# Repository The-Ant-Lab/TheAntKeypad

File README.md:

# TheAntKeypad
The Ant Keypad project: hardware, firmware and software.

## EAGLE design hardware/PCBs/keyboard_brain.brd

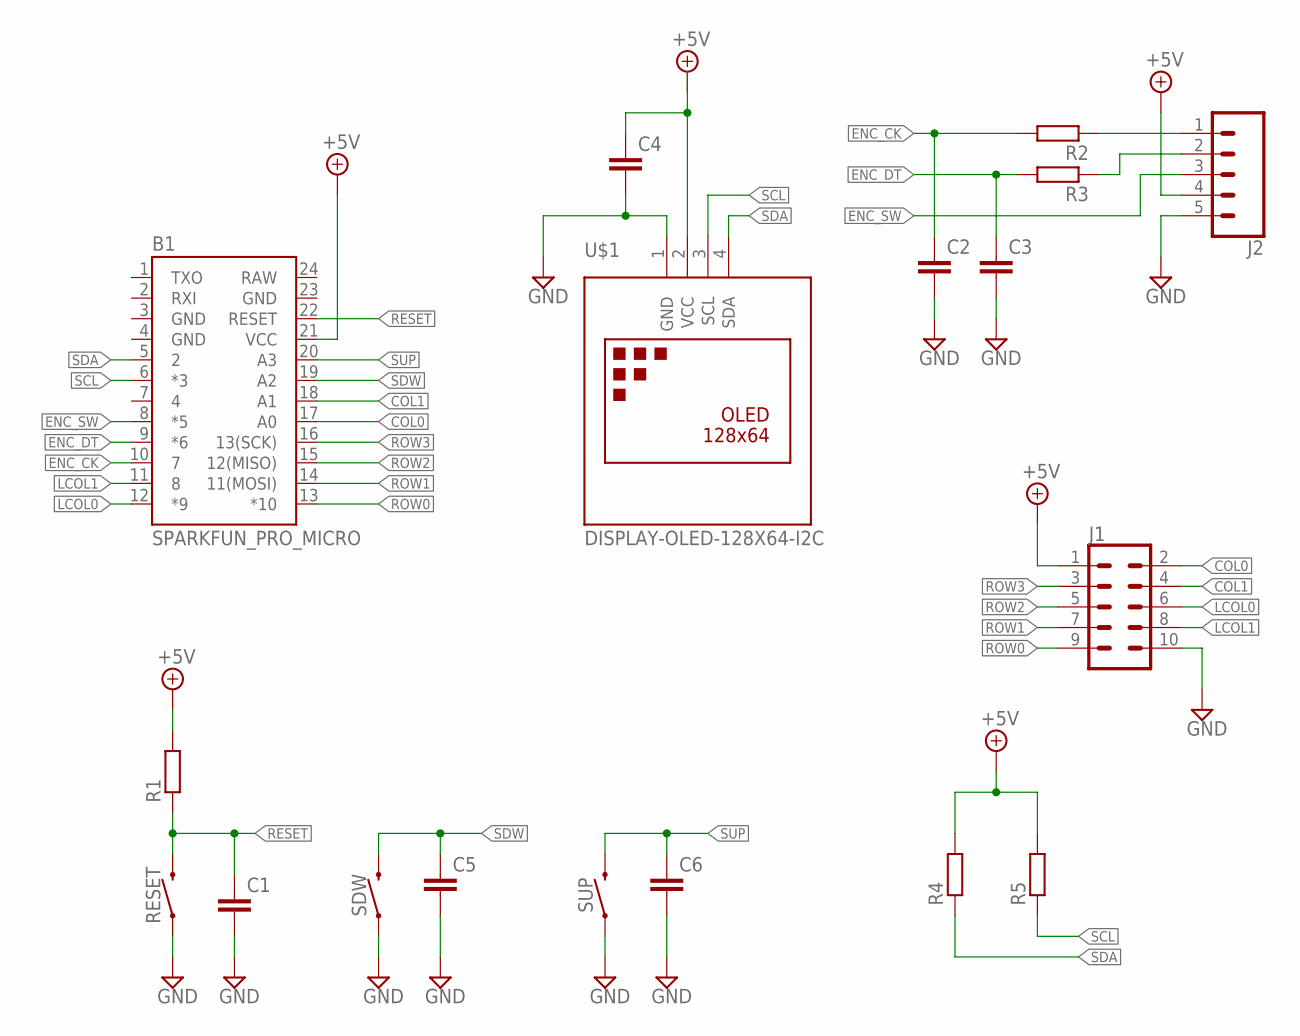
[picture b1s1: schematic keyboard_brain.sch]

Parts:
B1: SPARKFUN_PRO_MICRO
C1, C2, C3, C4, C5, C6: C-EUC0603K; C0603K
J1: CONN_05X2PTH; 2X5
J2: CONN_05; 1X05
R1, R2, R3, R4, R5: R-EU_R0603; R0603
RESET: MOMENTARY-SWITCH-SPST-PTH-6.0MM; TACTILE_SWITCH_PTH_6.0MM
SDW: MOMENTARY-SWITCH-SPST-SMD-5.2-REDUNDANT; TACTILE_SWITCH_SMD_5.2MM
SUP: MOMENTARY-SWITCH-SPST-SMD-5.2-REDUNDANT; TACTILE_SWITCH_SMD_5.2MM
U$1: DISPLAY-OLED-128X64-I2C

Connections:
+5V: B1.21 (VCC), C4.1, J1.1, J2.4, R1.2, R4.2, R5.2, U$1.2 (VCC)
COL0: B1.17 (A0), J1.2
COL1: B1.18 (A1), J1.4
ENC_CK: B1.10 (7), C2.1, R2.2
ENC_DT: B1.9 (*6), C3.1, R3.2
ENC_SW: B1.8 (*5), J2.3
GND: B1.3 (GND), B1.4 (GND), B1.23 (GND), C1.2, C2.2, C3.2, C4.2, C5.2, C6.2, J1.10, J2.5, RESET.1, SDW.1, SDW.2 (1), SUP.1, SUP.2 (1), U$1.1 (GND)
LCOL0: B1.12 (*9), J1.6
LCOL1: B1.11 (8), J1.8
unnamed: J2.1, R2.1
unnamed: J2.2, R3.1
RAW: B1.24 (RAW)
RESET: B1.22 (RESET), C1.1, R1.1, RESET.3 (2)
ROW0: B1.13 (*10), J1.9
ROW1: B1.14 (11(MOSI)), J1.7
ROW2: B1.15 (12(MISO)), J1.5
ROW3: B1.16 (13(SCK)), J1.3
SCL: B1.6 (*3), R5.1, U$1.3 (SCL)
SDA: B1.5 (2), R4.1, U$1.4 (SDA)
SDW: B1.19 (A2), C5.1, SDW.3 (2), SDW.4 (2)
SUP: B1.20 (A3), C6.1, SUP.3 (2), SUP.4 (2)

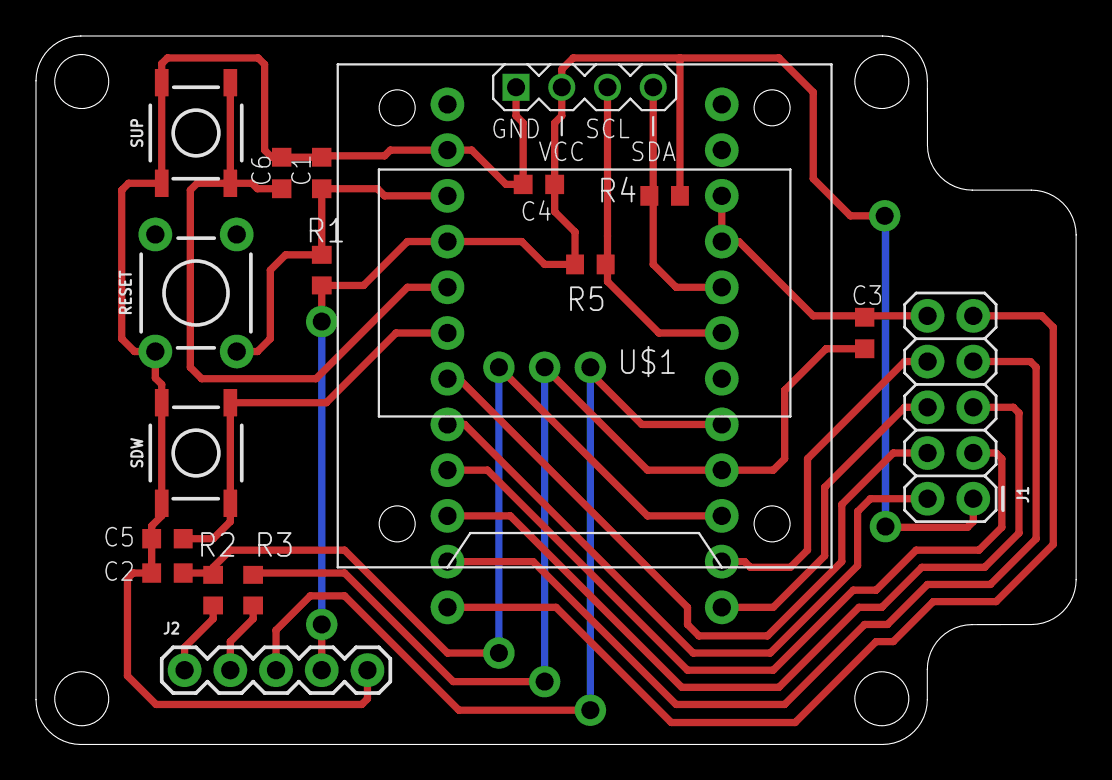
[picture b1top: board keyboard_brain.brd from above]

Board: 2 copper layers, 57.8 x 39.4 mm, 18 parts (1 on the bottom side), 20 nets.

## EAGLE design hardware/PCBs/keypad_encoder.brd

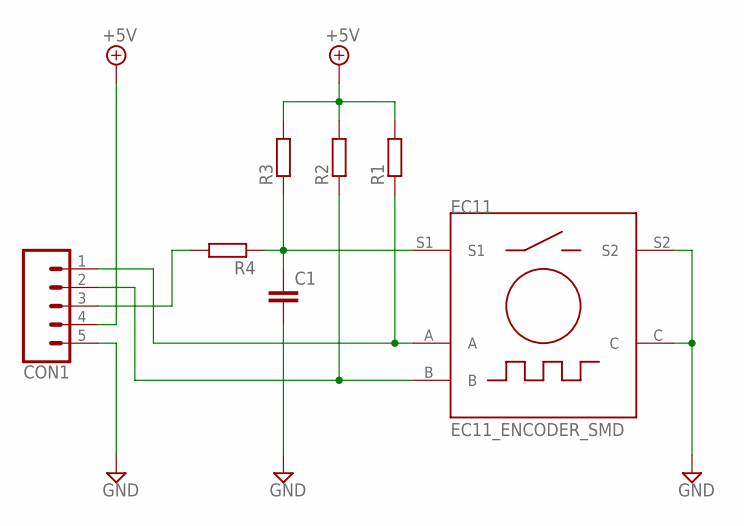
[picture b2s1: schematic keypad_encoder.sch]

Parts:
C1: C-EUC0603; C0603
CON1: CONN_05; 1X05
EC11: EC11_ENCODER_SMD; EC11_SMD
R1, R2, R3, R4: R-EU_R0603; R0603

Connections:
+5V: CON1.4, R1.2, R2.2, R3.2
GND: C1.2, CON1.5, EC11.C, EC11.S2
unnamed: C1.1, EC11.S1, R3.1, R4.1
unnamed: CON1.2, EC11.B, R2.1
unnamed: CON1.1, EC11.A, R1.1
unnamed: CON1.3, R4.2

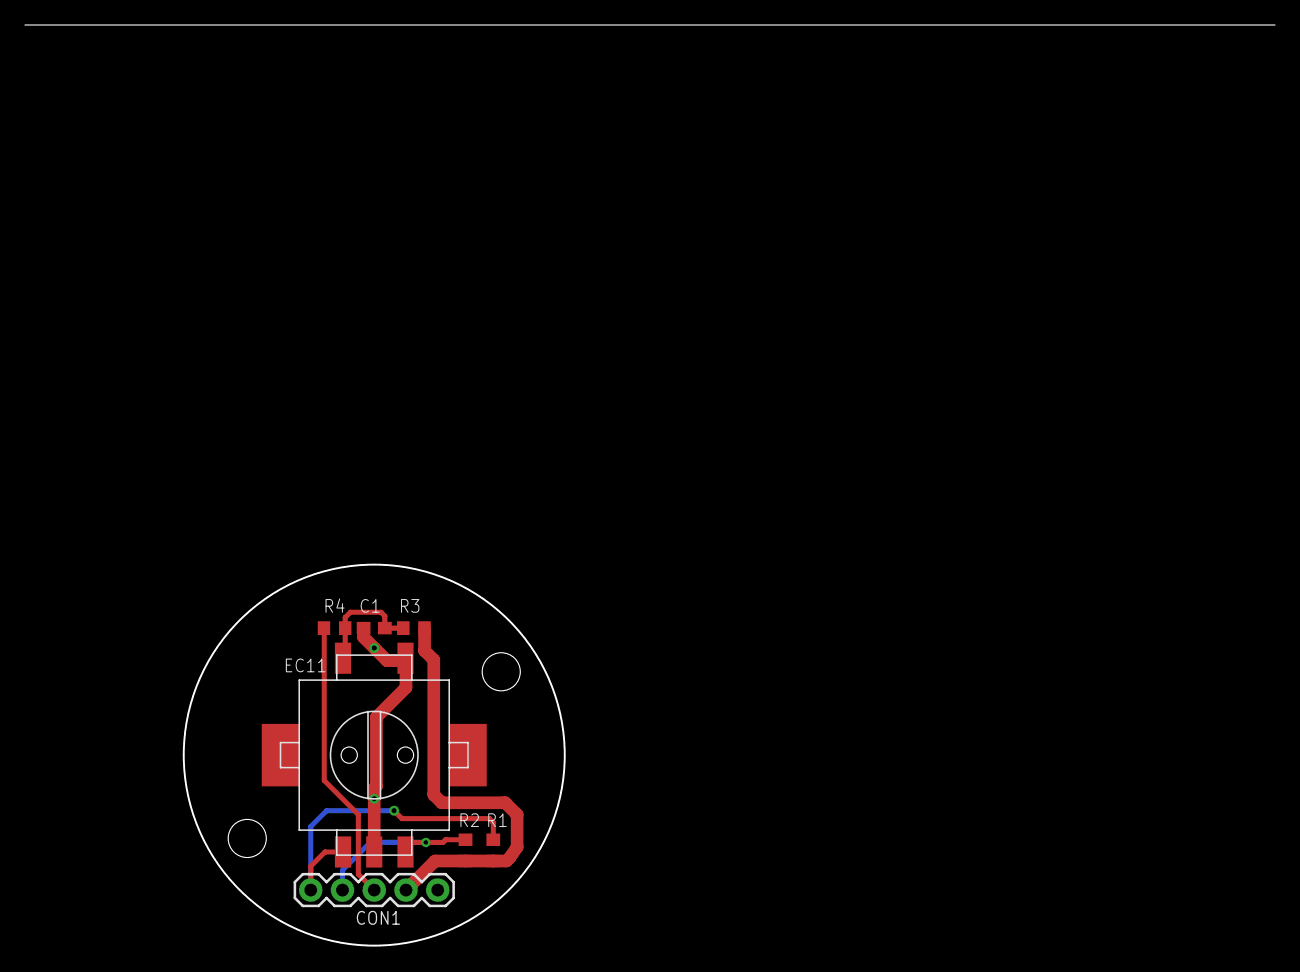
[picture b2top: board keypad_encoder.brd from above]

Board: 2 copper layers, 99.8 x 73.6 mm, 7 parts (0 on the bottom side), 6 nets.

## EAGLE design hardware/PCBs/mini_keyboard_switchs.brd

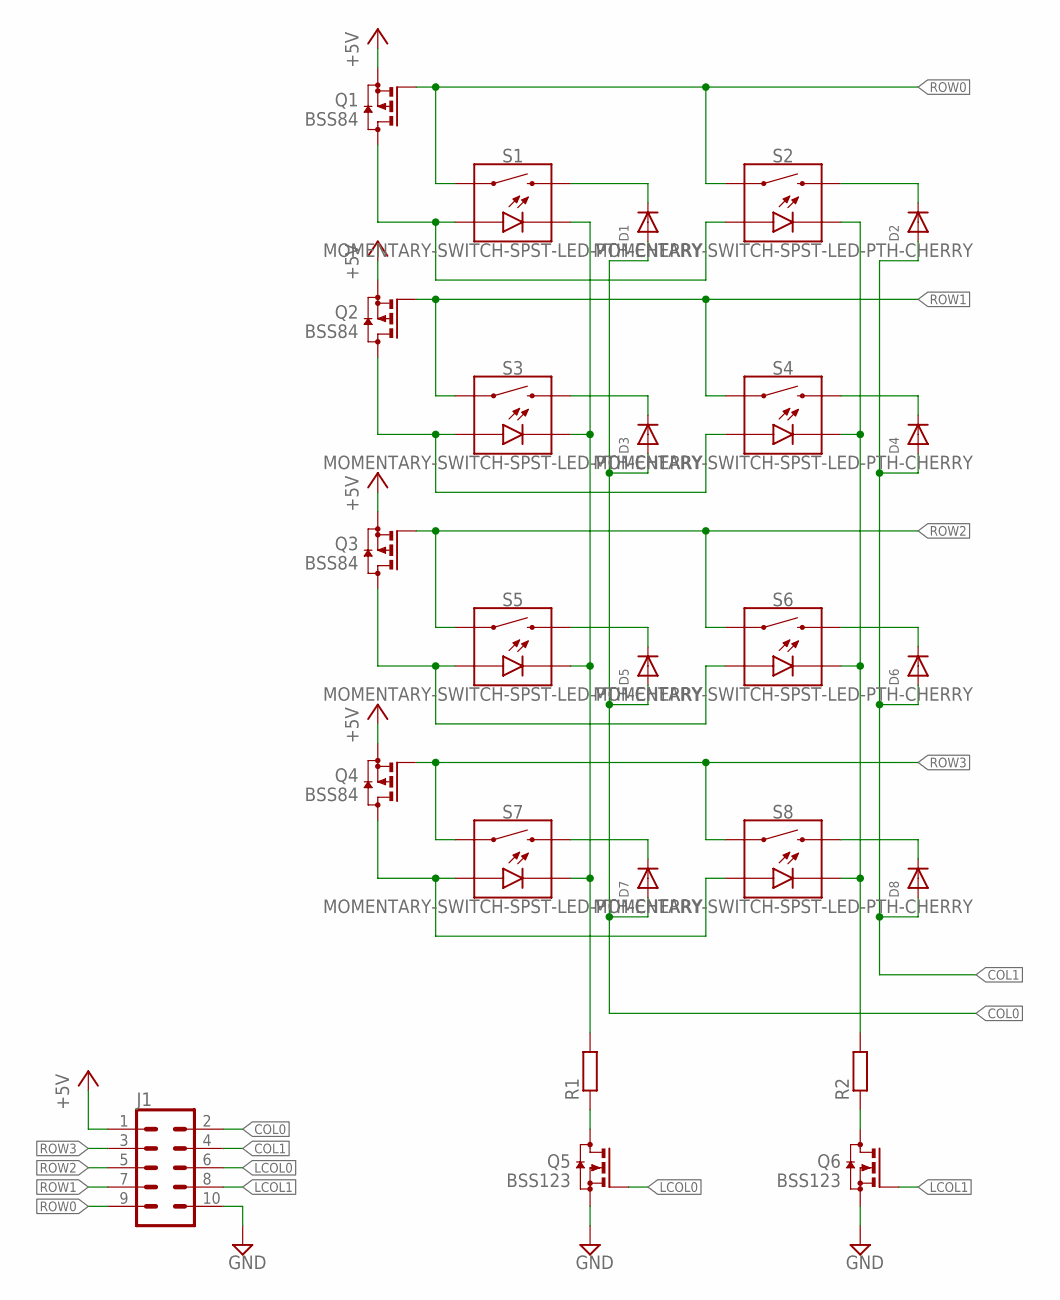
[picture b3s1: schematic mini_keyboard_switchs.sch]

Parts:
D1, D2, D3, D4, D5, D6, D7, D8: DIODESOD-323F; SOD-323F
J1: CONN_05X2PTH; 2X5
Q1, Q2, Q3, Q4: BSS84; SOT23
Q5, Q6: BSS123; SOT23
R1, R2: R-EU_R0603; R0603
S1, S2, S3, S4, S5, S6, S7, S8: MOMENTARY-SWITCH-SPST-LED-PTH-CHERRY; CHERRY-MX-LED

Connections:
+5V: J1.1, Q1.2 (S), Q2.2 (S), Q3.2 (S), Q4.2 (S)
COL0: D1.A, D3.A, D5.A, D7.A, J1.2
COL1: D2.A, D4.A, D6.A, D8.A, J1.4
GND: J1.10, Q5.2 (S), Q6.2 (S)
LCOL0: J1.6, Q5.1 (G)
LCOL1: J1.8, Q6.1 (G)
unnamed: D7.C, S7.S2 (2)
unnamed: Q4.3 (D), S7.A, S8.A
unnamed: D8.C, S8.S2 (2)
unnamed: D1.C, S1.S2 (2)
unnamed: D3.C, S3.S2 (2)
unnamed: D5.C, S5.S2 (2)
unnamed: D2.C, S2.S2 (2)
unnamed: D4.C, S4.S2 (2)
unnamed: D6.C, S6.S2 (2)
unnamed: Q3.3 (D), S5.A, S6.A
unnamed: Q5.3 (D), R1.1
unnamed: Q6.3 (D), R2.1
unnamed: Q2.3 (D), S3.A, S4.A
unnamed: Q1.3 (D), S1.A, S2.A
unnamed: R1.2, S1.K (C), S3.K (C), S5.K (C), S7.K (C)
unnamed: R2.2, S2.K (C), S4.K (C), S6.K (C), S8.K (C)
ROW0: J1.9, Q1.1 (G), S1.S1 (1), S2.S1 (1)
ROW1: J1.7, Q2.1 (G), S3.S1 (1), S4.S1 (1)
ROW2: J1.5, Q3.1 (G), S5.S1 (1), S6.S1 (1)
ROW3: J1.3, Q4.1 (G), S7.S1 (1), S8.S1 (1)

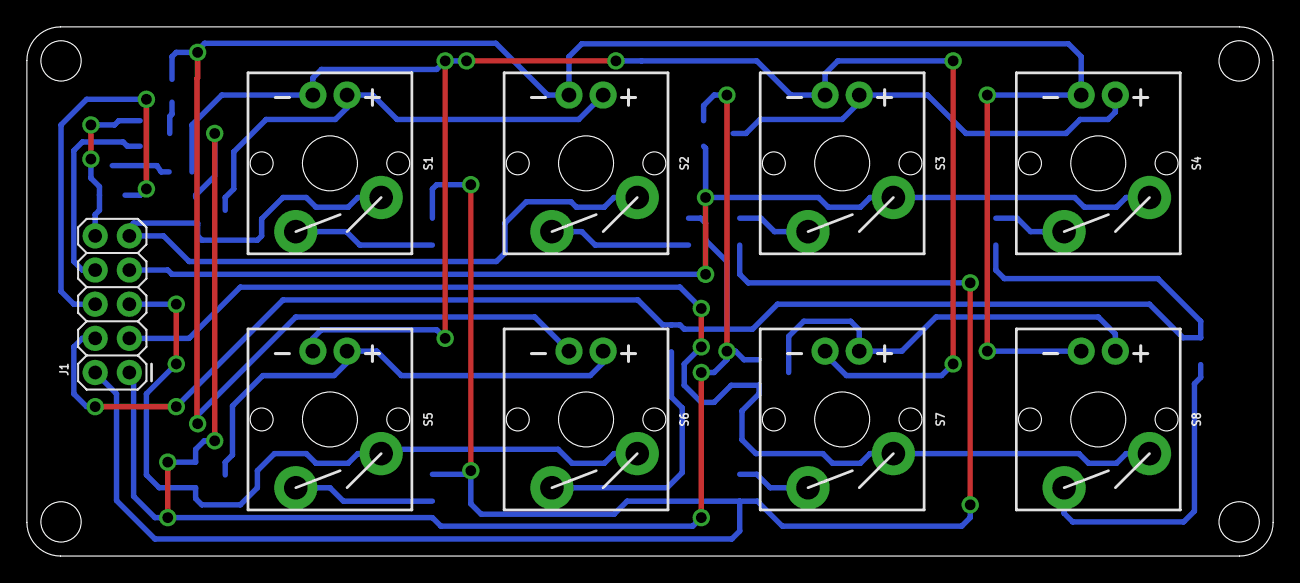
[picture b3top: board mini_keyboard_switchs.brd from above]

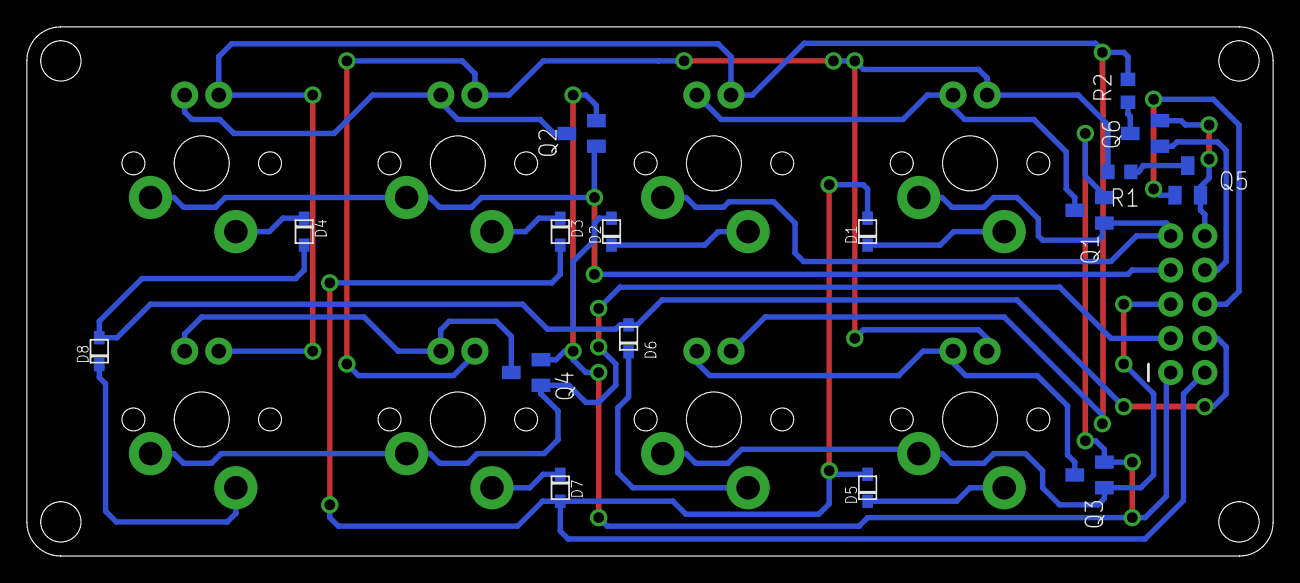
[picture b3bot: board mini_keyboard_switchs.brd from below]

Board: 2 copper layers, 92.7 x 39.4 mm, 25 parts (16 on the bottom side), 26 nets.

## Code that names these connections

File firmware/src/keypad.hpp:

//--------------------------------------
// Controllo Keypad
//--------------------------------------

#ifndef KEYPAD8_H
#define KEYPAD8_H

#include "arduino.h"

class MyKeypad
{
  private:
    
    uint8_t ROW0;
    uint8_t ROW1;
    uint8_t ROW2;
    uint8_t ROW3;
    uint8_t COL0;
    uint8_t COL1;
    uint8_t LCOL0;
    uint8_t LCOL1;
  
  public:

    MyKeypad(uint8_t row0_pin, uint8_t row1_pin, uint8_t row2_pin, uint8_t row3_pin, uint8_t col0_pin, uint8_t col1_pin, uint8_t lcol0_pin, uint8_t lcol1_pin);
    byte scan(void);

    char keys[9] = "12345678";

    byte key_state;
    byte key_pressed;
    byte key_released;
    byte key_prev_state;

};

#endif

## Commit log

2022-08-20 Adding first version of keypad firmware.
2022-08-20 Adding first host software version.
2022-08-20 Adding package requirements list.
2022-08-20 Adding first version of 3D parts.
2022-08-20 Adding first version of PCBs related files.

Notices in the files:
parts and their libraries:
SparkFun-Boards: Licensing: Creative Commons ShareAlike 4.0 International - https://creativecommons.org/licenses/by-sa/4.0
diy-modules_oled: Released under the Creative Commons Attribution 4.0 International License: http://creativecommons.org/licenses/by/4.0
